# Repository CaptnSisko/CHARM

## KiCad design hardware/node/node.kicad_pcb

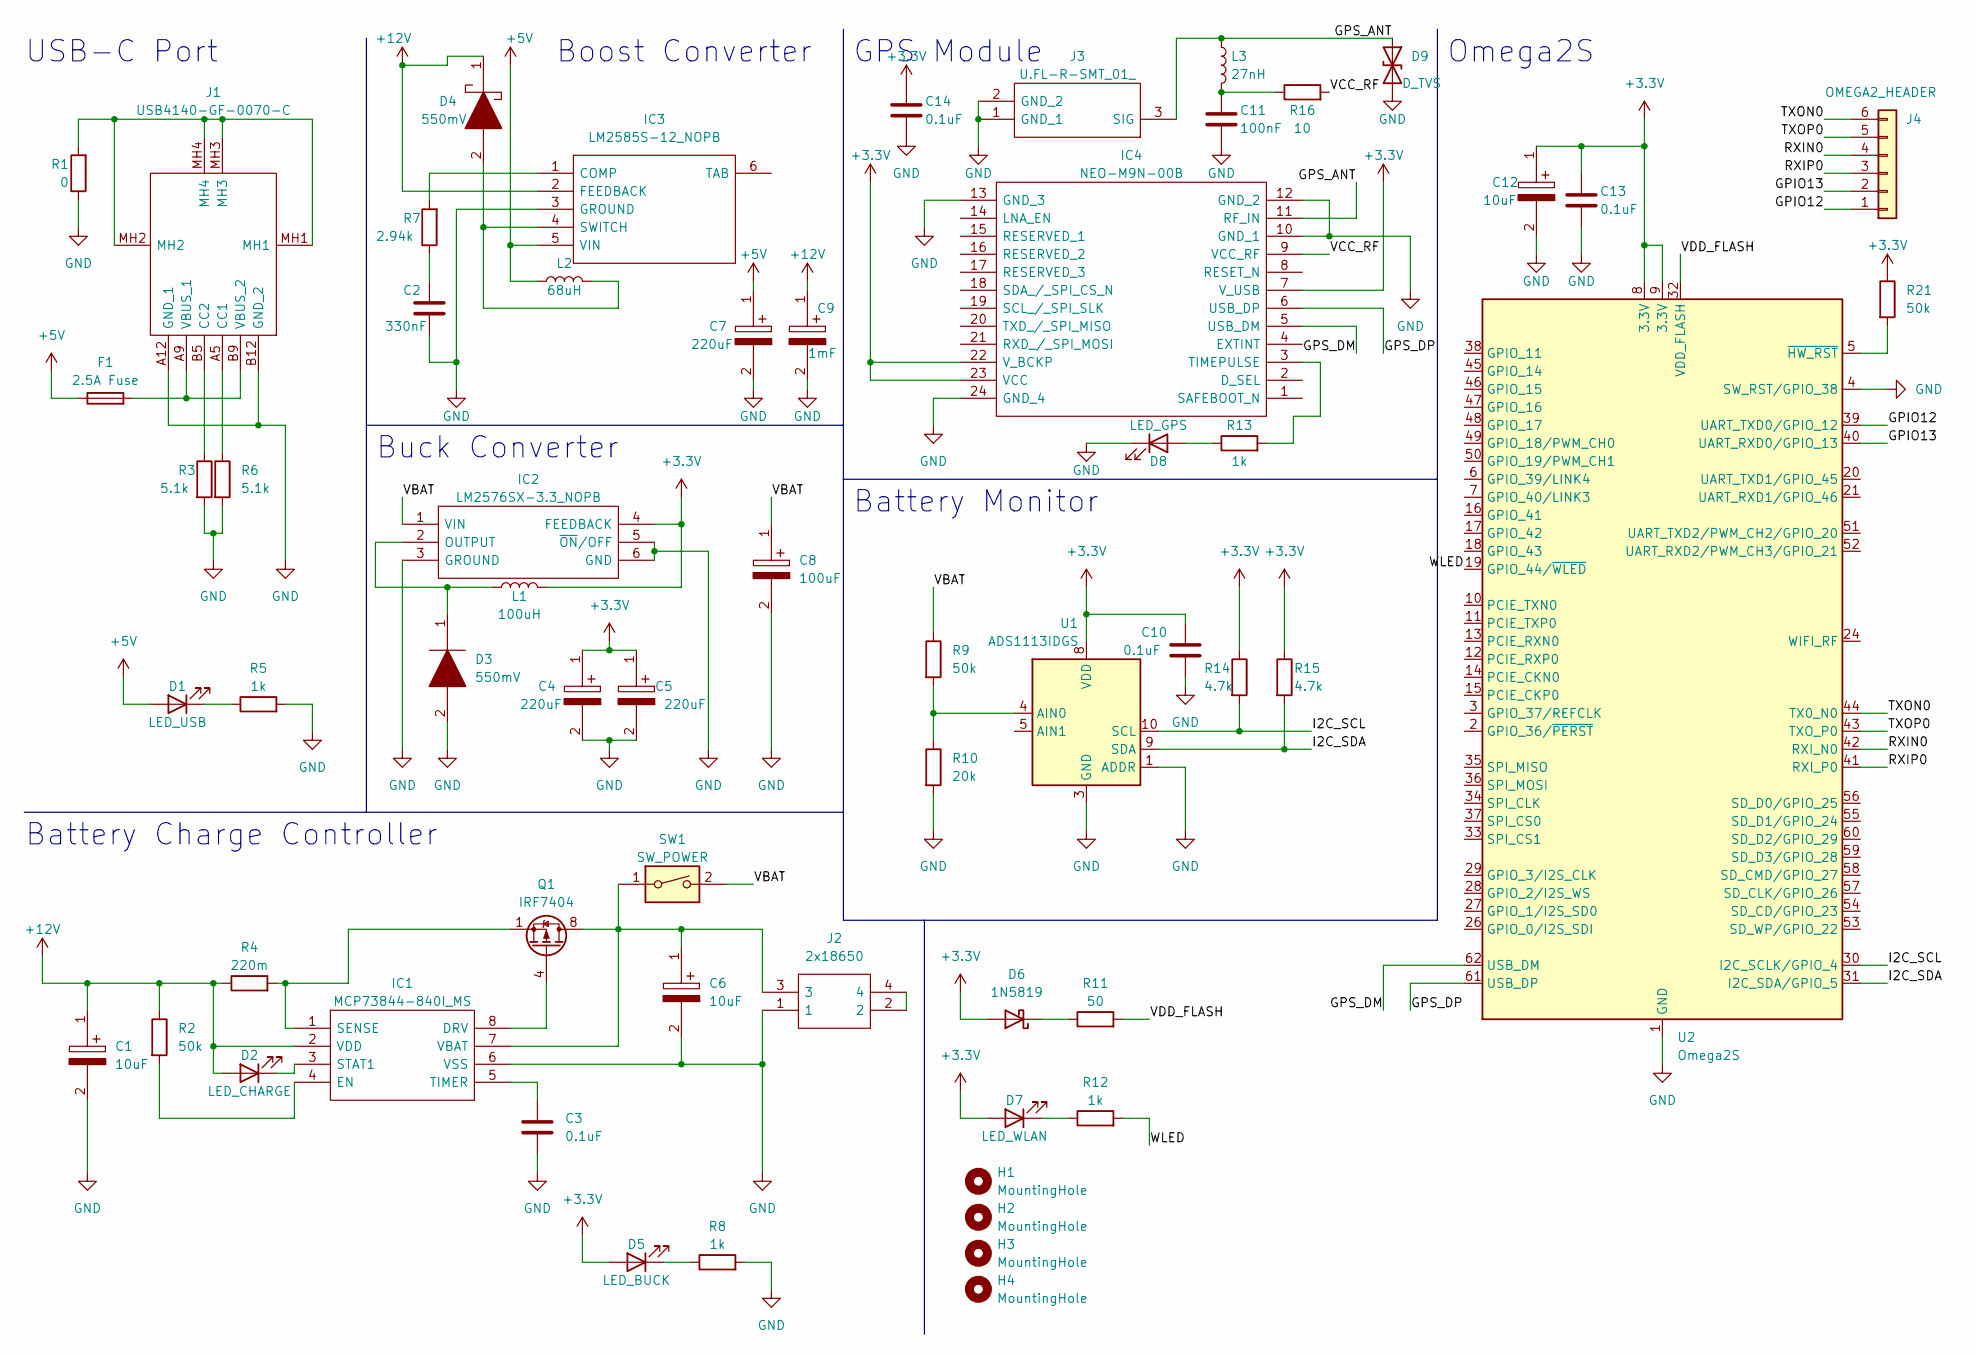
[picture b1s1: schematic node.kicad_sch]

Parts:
C1, C6, C12: 10uF; EEE1AA220WR; Manufacturer_Part_Number EEE-FN1E100R; Mouser Part Number 667-EEE-FN1E100R
C2: 330nF; C_1206_3216Metric_Pad1.33x1.80mm_HandSolder
C3, C10, C13, C14: 0.1uF; C_1206_3216Metric_Pad1.33x1.80mm_HandSolder
C4, C5, C7: 220uF; CAPAE660X800N; Manufacturer_Part_Number UUD1C221MCL1GS; Mouser Part Number 647-UUD1C221MCL
C8: 100uF; 16SVF180M; Manufacturer_Part_Number 16SVPC100M; Mouser Part Number 667-16SVPC100M
C9: 1mF; 16SVF1000M; Manufacturer_Part_Number 16SVPF1000M; Mouser Part Number 667-16SVPF1000M
C11: 100nF; C_0402_1005Metric_Pad0.74x0.62mm_HandSolder
D1: LED_USB; LED_0805_2012Metric_Pad1.15x1.40mm_HandSolder
D2: LED_CHARGE; LED_0805_2012Metric_Pad1.15x1.40mm_HandSolder
D3: 550mV; DIOM7959X250N; Manufacturer_Part_Number B520C-13-F; Mouser Part Number 621-B520C-F
D4: 550mV; SODFL3617X108N; Manufacturer_Part_Number SS24FL; Mouser Part Number 512-SS24FL
D5: LED_BUCK; LED_0805_2012Metric_Pad1.15x1.40mm_HandSolder
D6: 1N5819; D_A-405_P10.16mm_Horizontal
D7: LED_WLAN; LED_0805_2012Metric_Pad1.15x1.40mm_HandSolder
D8: LED_GPS; LED_0805_2012Metric_Pad1.15x1.40mm_HandSolder
D9: D_TVS; D_SOD-523
F1: 2.5A Fuse; Fuse_1206_3216Metric_Pad1.42x1.75mm_HandSolder
H1, H2, H3, H4: MountingHole; MountingHole_3.2mm_M3
IC1: MCP73844-840I_MS; SOP65P490X110-8N; Manufacturer_Part_Number MCP73844-840I/MS; Mouser Part Number 579-MCP73844-840I/MS
IC2: LM2576SX-3.3_NOPB; KTT0005B; Manufacturer_Part_Number LM2576SX-3.3/NOPB; Mouser Part Number 926-LM2576SX33NOPB
IC3: LM2585S-12_NOPB; TO170P1435X465-6N; Manufacturer_Part_Number LM2585S-12/NOPB; Mouser Part Number 926-LM2585S-12/NOPB
IC4: NEO-M9N-00B; NEOM9N00B; Manufacturer_Part_Number NEO-M9N-00B; Mouser Part Number 377-NEO-M9N-00B
J1: USB4140-GF-0070-C; USB4140GF0070C; Manufacturer_Part_Number USB4140-GF-0070-C; Mouser Part Number 640-USB4140-GF-0070C
J2: 2x18650; 1123; Manufacturer_Part_Number 1123; Mouser Part Number 534-1123
J3: U.FL-R-SMT_01_; UFLRSMT01; Manufacturer_Part_Number U.FL-R-SMT(01); Mouser Part Number 798-U.FL-R-SMT01
J4: OMEGA2_HEADER; PinSocket_1x06_P2.00mm_Vertical
L1: 100uH; 74437429203101
L2: 68uH; INDPM120120X1020N
L3: 27nH; L_0603_1608Metric_Pad1.05x0.95mm_HandSolder
Q1: IRF7404; SOIC-8_3.9x4.9mm_P1.27mm
R1: 0; R_0603_1608Metric_Pad0.98x0.95mm_HandSolder
R2, R9, R21: 50k; R_0603_1608Metric_Pad0.98x0.95mm_HandSolder
R3, R6: 5.1k; R_0603_1608Metric_Pad0.98x0.95mm_HandSolder
R4: 220m; R_0805_2012Metric_Pad1.20x1.40mm_HandSolder
R5, R8, R12, R13: 1k; R_0603_1608Metric_Pad0.98x0.95mm_HandSolder
R7: 2.94k; R_0603_1608Metric_Pad0.98x0.95mm_HandSolder
R10: 20k; R_0603_1608Metric_Pad0.98x0.95mm_HandSolder
R11: 50; R_0603_1608Metric_Pad0.98x0.95mm_HandSolder
R14, R15: 4.7k; R_0603_1608Metric_Pad0.98x0.95mm_HandSolder
R16: 10; R_1206_3216Metric_Pad1.30x1.75mm_HandSolder
SW1: SW_POWER; CKC5106-ND
U1: ADS1113IDGS; TSSOP-10_3x3mm_P0.5mm
U2: Omega2S; Onion_Omega2S

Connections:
+3.3V: C4.1, C5.1, C10.1, C12.1, C13.1, C14.1, D5.2 (A), D6.2 (A), D7.2 (A), IC2.4 (FEEDBACK), IC4.7 (V_USB), IC4.22 (V_BCKP), IC4.23 (VCC), L1.2, R14.1, R15.1, R21.1, U1.8 (VDD), U2.8 (3.3V), U2.9 (3.3V)
+5V: C7.1, D1.2 (A), F1.1, IC3.5 (VIN), L2.1
+12V: C1.1, C9.1, D2.2 (A), D4.1, IC1.2 (VDD), IC3.2 (FEEDBACK), R2.1, R4.1
/GPIO12: J4.1, U2.39 (UART_TXD0/GPIO_12)
/GPIO13: J4.2, U2.40 (UART_RXD0/GPIO_13)
/GPS_ANT: D9.1 (A1), IC4.11 (RF_IN), J3.3 (SIG), L3.1
/GPS_DM: IC4.5 (USB_DM), U2.62 (USB_DM)
/GPS_DP: IC4.6 (USB_DP), U2.61 (USB_DP)
/I2C_SCL: R14.2, U1.10 (SCL), U2.30 (I2C_SCLK/GPIO_4)
/I2C_SDA: R15.2, U1.9 (SDA), U2.31 (I2C_SDA/GPIO_5)
/RXIN0: J4.4, U2.42 (RXI_N0)
/RXIP0: J4.3, U2.41 (RXI_P0)
/TXON0: J4.6, U2.44 (TX0_N0)
/TXOP0: J4.5, U2.43 (TXO_P0)
/VBAT: C8.1, IC2.1 (VIN), R9.1, SW1.2
/VCC_RF: IC4.9 (VCC_RF), R16.2
/VDD_FLASH: R11.2, U2.32 (VDD_FLASH)
/WLED: R12.2, U2.19 (GPIO_44/~WLED)
GND: C1.2, C2.2, C3.2, C4.2, C5.2, C6.2, C7.2, C8.2, C9.2, C10.2, C11.2, C12.2, C13.2, C14.2, D3.2, D8.1 (K), D9.2 (A2), IC1.6 (VSS), IC2.3 (GROUND), IC2.5 (~ON/OFF), IC2.6 (GND), IC3.3 (GROUND), IC4.10 (GND_1), IC4.12 (GND_2), IC4.13 (GND_3), IC4.24 (GND_4), J1.A12 (GND_1), J1.B12 (GND_2), J2.1, J3.1 (GND_1), J3.2 (GND_2), R1.1, R3.2, R5.2, R6.2, R8.2, R10.2, U1.1 (ADDR), U1.3 (GND), U2.1 (GND), U2.4 (SW_RST/GPIO_38), U2.22 (GND), U2.23 (GND), U2.25 (GND), U2.63 (GND), U2.64 (GND)
unnamed: C2.1, R7.1
unnamed: C3.1, IC1.5 (TIMER)
unnamed: C6.1, IC1.7 (VBAT), J2.3, Q1.5 (D), Q1.6 (D), Q1.7 (D), Q1.8 (D), SW1.1
unnamed: C11.1, L3.2, R16.1
unnamed: D1.1 (K), R5.1
unnamed: D2.1 (K), IC1.3 (STAT1)
unnamed: D3.1, IC2.2 (OUTPUT), L1.1
unnamed: D4.2, IC3.4 (SWITCH), L2.2
unnamed: D5.1 (K), R8.1
unnamed: D6.1 (K), R11.1
unnamed: D7.1 (K), R12.1
unnamed: D8.2 (A), R13.1
unnamed: F1.2, J1.A9 (VBUS_1), J1.B9 (VBUS_2)
unnamed: IC1.1 (SENSE), Q1.1 (S), Q1.2 (S), Q1.3 (S), R4.2
unnamed: IC1.4 (EN), R2.2
unnamed: IC1.8 (DRV), Q1.4 (G)
unnamed: IC3.1 (COMP), R7.2
unnamed: IC4.3 (TIMEPULSE), R13.2
unnamed: J1.A5 (CC1), R6.1
unnamed: J1.B5 (CC2), R3.1
unnamed: J1.MH1, J1.MH2, J1.MH3, J1.MH4, R1.2
unnamed: J2.2, J2.4
unnamed: R9.2, R10.1, U1.4 (AIN0)
unnamed: R21.2, U2.5 (~HW_RST)

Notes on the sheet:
Boost Converter
Buck Converter
Battery Monitor
GPS Module
Battery Charge Controller
USB-C Port
Omega2S

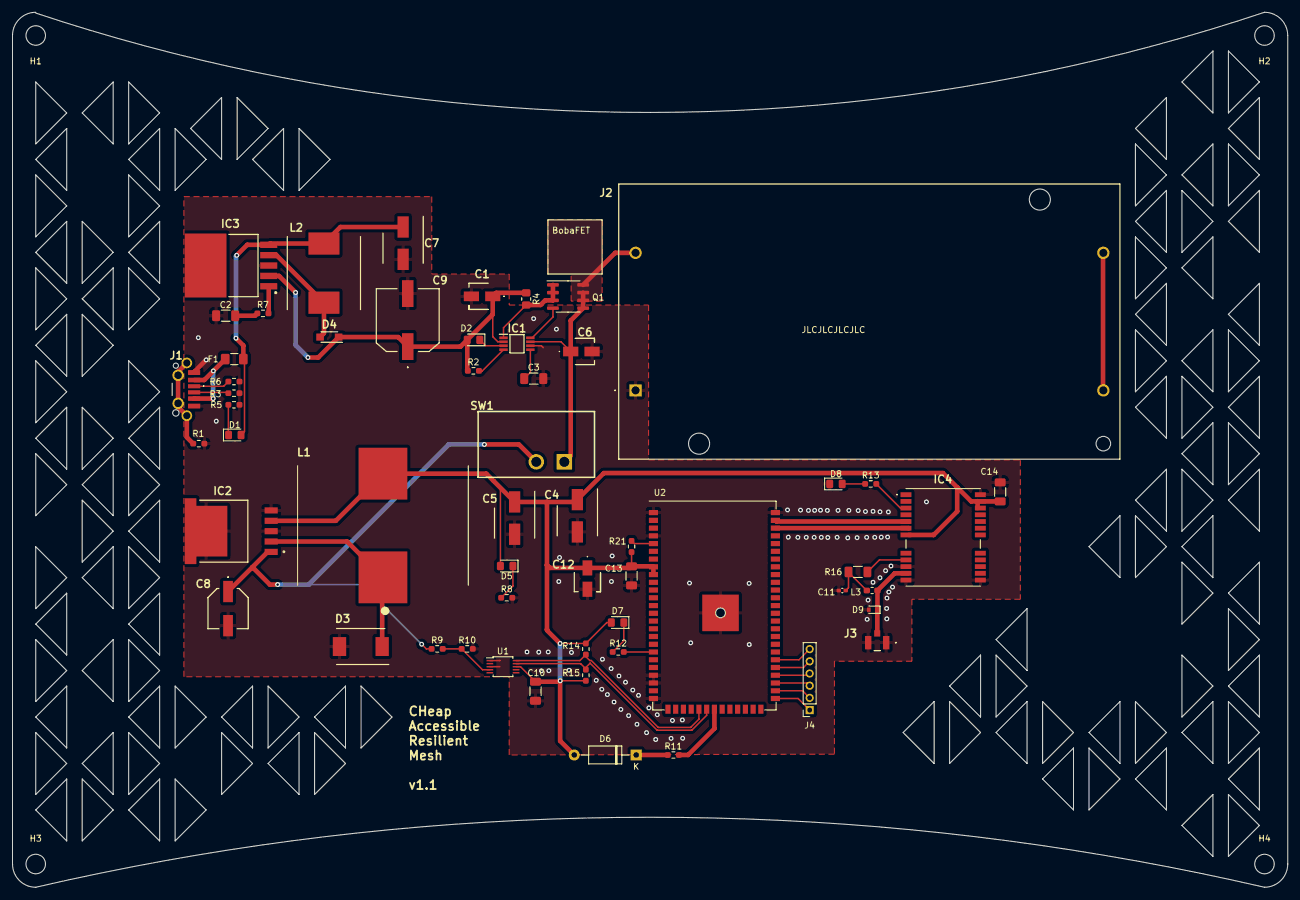
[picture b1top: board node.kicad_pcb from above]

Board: 2 copper layers, 209.1 x 143.4 mm, 60 parts (0 on the bottom side), 43 nets.

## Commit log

2022-08-29 Initial repo structure
2022-08-29 Marty initial notebook push
2022-08-30 publish notebook
2022-08-31 add react js template
2022-08-31 fix homepage url
2022-08-31 starter express js code
2022-08-31 add database code
2022-09-01 Martin notebook update
2022-09-02 Notes on basic functional react
2022-09-02 Implemented ugly hamburger
2022-09-02 Added Google Map to application and removed Strict Mode to get Google Map working
2022-09-02 Added styling for GoogleMaps, removed padding around map
2022-09-02 Changed map to start by pointing at the north quad
2022-09-02 Created 2 components for nodes on the map and corresponding cards in the sidebar
2022-09-02 Changed text for the nodes on the map to router icons
2022-09-03 Finished node cards without error handling
2022-09-03 Finished node cards
2022-09-06 cloud infra notebook entry
2022-09-06 first half hardware notebook entry
2022-09-06 battery charge controller doc
2022-09-06 finish notebook entry
2022-09-07 Got very basic tooltips running
2022-09-07 Removed TODO which was addressed already
2022-09-07 Added TODO for properly popup state handling
2022-09-08 Added timing state to App.js and not sub-components
2022-09-08 Code formatting changes, removal of unused imports
2022-09-08 Started working on popup locking logic
2022-09-09 Finished node tooltip creation
2022-09-09 remove addressed TODO
2022-09-09 Fixed bugwith node icon clicking
2022-09-09 Downgrade to react v17
2022-09-09 Fixed rendering error and made necessary node card adjustments
2022-09-11 update to in-stock components
2022-09-11 update boost converter
2022-09-11 USB Validation
2022-09-11 Fixed notebook formatting issue
2022-09-11 fix missing connection in boost converter
2022-09-12 Notebook update with system monitor work
2022-09-13 upload design reports
2022-09-22 Basic inital setup
2022-09-22 Saved progress with database integration
2022-09-23 Finished the setup of the database, taking notes on all SQL commands used
2022-09-23 Finished the GET method
2022-09-23 updated the get function to use data format expected
2022-09-24 Finished the backend code and rough data validation
2022-09-24 Updated notebook with notes about work done today
2022-09-25 fix schematic naming, remove hard reset circuit
2022-09-27 push latest hardware changes (TODO: active GPS antenna)
2022-09-27 import component footprints / symbols
2022-09-27 finish capacitor part selection and footprint assignment
2022-10-04 PCB Layout
2022-10-05 finalize PCB
2022-10-06 Added react query and removed API key requirement for the GET data endpoint
2022-10-06 Initial version of frontend linkup finished
2022-10-06 Added polling of API for frontend to reflect most recent backend state
2022-10-06 App.js formatting fices
2022-10-06 Removal of mock data
2022-10-06 Minor backend formatting changes
2022-10-06 Trying to make sure things don't explode in production
2022-10-06 Addition of preview URI to cors whitelist
2022-10-19 fix PCB dimensions to fit new case, remove USB series resistors from schematic
2022-10-19 Updated Marty notebook
2022-10-19 Update notebook with setup instructions
2022-10-19 push latest PCB
2022-10-19 print database errors to console
2022-10-19 Last changes to master, sorry trevor lol
2022-10-19 use https for backend requests
2022-10-20 Wrote the first xcompilable program for the Omega, helloWorld
2022-10-20 Updated notebook with Omega2S+ Xcompilation environment setup instructions
2022-10-21 Finished ADC reading logic
2022-10-21 Started interfacing with the GPS
2022-10-21 Data analysis on the ADC voltages
2022-10-21 Added data point from ADC with batteries
2022-10-21 Finished some notes on NMEA sentence parsing
2022-10-22 Setting up testing workflow
2022-10-22 Added checksum function
2022-10-22 Finished prefix extraction
2022-10-22 Finished rough gps parse
2022-10-22 Finished everything other than validation for analysis
2022-10-23 Fixed error in analysis
2022-10-23 Finished ADC analysis
2022-10-24 push some notebook
2022-10-24 PCB Layout Sections
2022-10-24 add pcb layout to notebook
2022-10-25 Added charging system stress test information
2022-10-25 Added .tex file for the soldering guide ahead of PCB delivery
2022-10-25 Progress on battery soldering manual
2022-10-25 Finished section with buck converter
2022-10-25 Finished omega 2s+ soldering section
2022-10-26 Finished everything expcept for quality assurance in the soldering guide
2022-10-26 Working on quality assurance procedures
2022-10-26 Finished my portion of the soldering guide
2022-11-05 Updating notebook
2022-11-05 Refactored the GPS code
2022-11-05 Finished GPS refactor
2022-11-05 updated notes
2022-11-06 Updated notebook
2022-11-06 Fixed bug in refactored code
2022-11-19 initial update
2022-11-20 Added notes on wifi range extension setup
2022-11-21 Added some notes for networking attempts with BATMAN
2022-11-23 Upload of config files for networking
2022-11-23 Working on meshing
2022-11-23 Created script for automating AP setup
2022-11-23 Changed installation scripts for AP
2022-11-23 Updated script names for clarity
2022-11-23 Pushing gateway installation files
2022-11-23 Updated readmen
2022-11-23 Updated notebook before starting telemetry coding
2022-11-23 Old telemetry scripting
2022-11-23 upload os compilation instructions
2022-11-23 fix file path
2022-11-23 Progress in developing telemetry pkg
2022-11-23 Added dockerfile
2022-11-23 Created dockerfile to build image for openwrt compilation
2022-11-23 Updated docker file and notes about the build system
2022-11-24 Minor readme updates
2022-11-24 Progress in working on telemetry service
2022-11-24 Finished post script
2022-11-24 Remove backend key from github
2022-11-24 Fixed small typo, updated readme
2022-11-24 Changed script to use absolute key path
2022-11-24 mobile support: change sidebar width to 1/3 of monitor size
2022-11-24 Changing up of installation scripts
2022-11-24 Update installation scripts and config with SSID for APs
2022-11-24 Finished telemetry raw scripts
2022-11-24 Updated raw download links for config files
2022-11-24 Updated setup scripts
2022-11-24 Update post script initialization procedure
2022-11-24 Updated installation script
2022-11-24 Install script for the gateway
2022-11-24 Fixed post script bug
2022-11-24 Update install instrucitons
2022-11-24 Update install instructions
2022-11-24 Updated ap installation instruction to somewhat final version
2022-11-24 Update with installation instructions for the gateway
2022-11-28 Update notebooks
2022-11-28 add new gateway config
2022-11-29 update mtu
2022-11-29 Notes from final system testing
2022-11-29 Updated the post script to send 0, 0 when no GPS lock avaialbel
2022-11-29 Updated post script
2022-11-29 Updated the telemetry executable
2022-11-29 update monitor to support missing location
2022-11-29 update to support no location
2022-11-29 attmept to fix sql error
2022-11-29 fix error to allow missing lat and lng
2022-11-29 sort list of nodes
2022-11-29 Added notes for things to do after dinner
2022-11-29 Added note to take multimeter to demo
2022-11-30 Update the post script for a390
2022-12-08 Update README.md
    copy and paste onenote to github format
